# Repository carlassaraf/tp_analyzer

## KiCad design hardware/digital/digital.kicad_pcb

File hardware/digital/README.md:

# Placa digital: ADC de picos y expansor de E/S

Esta placa es el punto de unión entre las 4 placas analógicas (una por línea: L1, L2, L3 y N) y la placa del RP2350B. Todas las señales de las placas analógicas pasan por acá, así que hacia el RP2350B sale **un solo conector**.

- Esquemático: [digital.kicad_sch](digital.kicad_sch) (una hoja, A3).
- Placa analógica (una por línea): [../analog](../analog).

## 1. Qué hace

| Función | Cómo |
|---|---|
| Leer los detectores de pico (VPK, IPK) de las 4 líneas | Dos MCP3204 (12 bits, 4 canales, SPI): U2 para L1 y L2, U3 para L3 y N |
| Generar los 10 chip selects (8 MCP41010 + 2 MCP3204) sin usar pines del RP2350B | Expansor MCP23017 por I2C (U1) |
| Llevar las 8 señales del canal principal (VADC, IADC) al ADC del RP2350B | Pasan directo de J1–J4 a J5 |
| Repartir alimentación y SPI a las placas analógicas | J5 → J1–J4 |

```
 Placa analógica L1 ──┐ 2x07                                       2x13
 Placa analógica L2 ──┤   VADC, IADC ─────────────────────────────►┐
 Placa analógica L3 ──┤   VPK, IPK L1/L2 ──► U2 ──┐               │
 Placa analógica N  ──┘   VPK, IPK L3/N  ──► U3 ──┤ MISO          ├── J5 ──► RP2350B
              ▲  SCK/MOSI (33 Ω por línea) ◄────┤ SCK, MOSI        │         (ADC GPIO40-47,
              └─ CS_V, CS_I ◄── U1 MCP23017 ◄───┘ SDA, SCL ────────┘          SPI, I2C, 5 V, 3,3 V)
```

## 2. Conectores

### J1–J4: placas analógicas (2x07, IDC, cable plano)

Mismo pinout en la placa analógica. Cada señal analógica viaja entre dos GND del cable plano.

| Pin | Señal | Pin | Señal |
|---|---|---|---|
| 1 | VADC (canal principal de tensión) | 2 | GND |
| 3 | IADC (canal principal de corriente) | 4 | GND |
| 5 | VPK (detector de pico de tensión) | 6 | GND |
| 7 | IPK (detector de pico de corriente) | 8 | GND |
| 9 | SCK | 10 | MOSI |
| 11 | CS_V (MCP41010 de tensión) | 12 | CS_I (MCP41010 de corriente) |
| 13 | +3,3 V | 14 | +5 V |

J1 = L1, J2 = L2, J3 = L3, J4 = N. En el esquemático las redes llevan el sufijo de la línea: `VADC_L1`, `CS_I_N`, etc.

### J5: RP2350B (2x13, IDC)

| Pin | Señal | Pin | Señal |
|---|---|---|---|
| 1 | IADC_L1 | 2 | GND |
| 3 | VADC_L1 | 4 | GND |
| 5 | IADC_L2 | 6 | GND |
| 7 | VADC_L2 | 8 | GND |
| 9 | IADC_L3 | 10 | GND |
| 11 | VADC_L3 | 12 | GND |
| 13 | IADC_N | 14 | GND |
| 15 | VADC_N | 16 | GND |
| 17 | +5 V | 18 | SCK |
| 19 | +5 V | 20 | MISO |
| 21 | +3,3 V | 22 | MOSI |
| 23 | +3,3 V | 24 | SDA |
| 25 | GND | 26 | SCL |

Los pines 1–15 van a las entradas de ADC del RP2350B (GPIO40–47). Dentro de cada par, IADC va en el pin impar más bajo y VADC en el siguiente: es el orden en que llegan las pistas por el borde de la placa (ver [placa_pcb.md](placa_pcb.md)). El cable o adaptador hacia el devboard tiene que respetar esta tabla. La alimentación de todo el sistema analógico entra por J5.

Pines 17–26: la fila impar mira al borde de la placa y lleva solo alimentación y GND, que pasan por vía al lado del conector. La fila par mira al interior y lleva las cinco señales digitales, en el orden en que llegan a U2 y U1 sin cruzarse. En el cable plano cada señal digital queda entre dos hilos de alimentación o GND.

### J6: expansión (1x08)

GPB2–GPB7 del MCP23017 (libres), +3,3 V y GND.

## 3. Chip selects (MCP23017, dirección 0x20)

A2, A1 y A0 van a GND: dirección I2C **0x20**. RESET con pull-up de 10 kΩ (R9). INTA e INTB sin conectar.

| Pin del MCP23017 | Señal | Dispositivo |
|---|---|---|
| GPA0 | CS_V_L1 | MCP41010, canal de tensión L1 |
| GPA1 | CS_I_L1 | MCP41010, canal de corriente L1 |
| GPA2 | CS_V_L2 | MCP41010, canal de tensión L2 |
| GPA3 | CS_I_L2 | MCP41010, canal de corriente L2 |
| GPA4 | CS_V_L3 | MCP41010, canal de tensión L3 |
| GPA5 | CS_I_L3 | MCP41010, canal de corriente L3 |
| GPA6 | CS_V_N | MCP41010, canal de tensión N |
| GPA7 | CS_I_N | MCP41010, canal de corriente N |
| GPB0 | CS_ADC_L12 | U2, MCP3204 de picos de L1 y L2 |
| GPB1 | CS_ADC_L3N | U3, MCP3204 de picos de L3 y N |
| GPB2–GPB7 | — | Libres, en J6 |

- **Pull-ups de 10 kΩ en los 10 CS (R12–R21).** Después del encendido o de un reset, los pines del MCP23017 son entradas (alta impedancia). Sin pull-up, un CS podría quedar flotando en bajo y un MCP41010 tomaría basura del bus SPI como un cambio de ganancia. Con los pull-ups todo queda deseleccionado hasta que el firmware configura el expansor.
- **GPA7 y GPB7 son solo salida** en la hoja de datos actual del MCP23017. Acá se usan como salidas, así que no hay problema.

## 4. ADC de picos (MCP3204)

Cada MCP3204 lee las dos líneas que tiene al lado en la placa (U2: L1 y L2, U3: L3 y N), en lugar de separar tensión y corriente. Así los picos de cada par de conectores llegan juntos al ADC y se ahorran cruces en el ruteo (ver [placa_pcb.md](placa_pcb.md)). Para el firmware solo cambia el mapa de canales.

| ADC | CH0 | CH1 | CH2 | CH3 |
|---|---|---|---|---|
| U2 (L1, L2) | VPK_L1 | IPK_L1 | VPK_L2 | IPK_L2 |
| U3 (L3, N) | VPK_L3 | IPK_L3 | VPK_N | IPK_N |

- **VREF = 3,3 V, ratiométrico.** Las placas analógicas toman su 3,3 V de esta placa, y su VBIAS es 3,3 V / 2. Si el 3,3 V se mueve, VBIAS y la referencia se mueven juntos, y VBIAS sigue cayendo en ~2048 cuentas. El offset de cada canal (tolerancia del divisor de VBIAS y fuga del detector) se calibra midiendo sin señal.
- Rango: el detector entrega VBIAS + 0 a 1,3 V, o sea 1,65 a 2,95 V, dentro de 0–3,3 V. 1 LSB = 0,81 mV.
- **100 nF en cada entrada (C4–C7, C11–C14).** El capacitor de muestreo del MCP3204 (~20 pF) se carga de golpe al empezar la conversión; los 100 nF le dan esa carga sin que la tensión se mueva (20 pF / 100 nF → < 1 LSB). Con los 10 kΩ en serie de la placa analógica forman un filtro de τ = 1 ms, despreciable frente a la descarga del detector (0,47 s).
- **Desacople:** C8 / C15 (100 nF) en Vdd; C9 + C10 / C16 + C17 (1 µF + 100 nF) junto al pin Vref.
- **SPI ≤ 1 MHz** a 3,3 V (límite del MCP3204 con VDD = 2,7 V). Los MCP41010 aceptan hasta 10 MHz: el firmware configura la frecuencia por dispositivo.
- **MISO compartido.** Dout del MCP3204 queda en alta impedancia mientras CS está alto, así que U2 y U3 comparten MISO. Los MCP41010 no tienen salida SO. El ERC marca "Output–Output" entre los dos Dout; en el proyecto ese caso está bajado a advertencia porque es intencional.

## 5. SPI hacia las placas: 33 Ω en serie (R1–R8)

SCK y MOSI de cada línea pasan por 33 Ω (R1/R2 = L1, R3/R4 = L2, R5/R6 = L3, R7/R8 = N). El cable plano a cada placa es una línea de transmisión corta sin terminar. Sin resistencia, los flancos de SCK rebotan y pueden contar como un pulso de reloj extra en el MCP41010. Los 33 Ω, junto con la impedancia de salida del RP2350B, se acercan a la impedancia del cable y amortiguan el rebote. Además, cada línea queda aislada de las otras: un cortocircuito en un cable no tira abajo el SPI de todas.

## 6. I2C

Pull-ups de 4,7 kΩ en SDA y SCL (R10, R11). **No colocarlos si la placa del RP2350B ya tiene pull-ups** en ese bus. Con 4,7 kΩ y unos 100 pF de bus, 400 kHz funciona bien.

## 7. Consumo estimado (4 placas analógicas)

| Riel | Consumidor | Corriente |
|---|---|---|
| 3,3 V | Divisor de VBIAS, 4 × 165 µA | 0,7 mA |
| 3,3 V | MCP41010, 8 × ~1 µA | < 0,1 mA |
| 3,3 V | MCP3204, 2 × ~0,4 mA (convirtiendo) | 0,8 mA |
| 3,3 V | MCP23017 activo + un CS en bajo (0,33 mA) + I2C (0,7 mA en bajo) | ~2 mA |
| **3,3 V** | **Total** | **~4 mA** |
| 5 V | 3 LM358 por línea (~0,7 mA c/u) | 4 × 2 mA |
| 5 V | Pull-downs de 1 kΩ en las salidas de los LM358 (~1,65 mA c/u) | 4 × ~8 mA |
| **5 V** | **Total** | **~45 mA** |

C1 y C2 (10 µF) son la reserva de 3,3 V y 5 V en la entrada.

## 8. Notas para el firmware (Zephyr)

- Zephyr tiene drivers para los dos integrados: `microchip,mcp23017` (familia `mcp23xxx`, como controlador GPIO) y `microchip,mcp3204` (familia `mcp320x`, subsistema ADC).
- Los `cs-gpios` del bus SPI pueden apuntar a pines del MCP23017 (`<&mcp23017 0 GPIO_ACTIVE_LOW>`, etc.). Así los MCP3204 y los MCP41010 se declaran como dispositivos SPI normales.
- Cada transacción SPI cuesta dos escrituras I2C extra (bajar y subir el CS): unos 100–200 µs a 400 kHz. Alcanza para cambiar ganancias y para leer los picos cada ~100 ms. No sirve para muestreo rápido, que igual lo hace el ADC del RP2350B.
- Hay que configurar el MCP23017 (pines como salida en alto) antes de la primera transacción SPI. Hasta ese momento los pull-ups mantienen todo deseleccionado.

## 9. Lista de componentes

J1–J6 usan footprints de [tp_digital.pretty](tp_digital.pretty): los estándar con pads de 2,0 mm y agujero de 1,0 mm, para agujerear a mano.

R1, R3, R5, R6, R7, R10 y R20, y los capacitores C4, C7, C12 y C13, tienen pistas que pasan entre sus pads. Por eso las resistencias son 1206: no reemplazarlas ni a ellas ni a los capacitores por un tamaño menor (ver [placa_pcb.md](placa_pcb.md), sección 4).

| Ref. | Valor | Tipo | Función |
|---|---|---|---|
| U1 | MCP23017-E/SO | SOIC-28W | Expansor de E/S I2C (chip selects) |
| U2, U3 | MCP3204-CI/SL | SOIC-14 | ADC de picos (U2: L1 y L2, U3: L3 y N) |
| J1–J4 | 2x07 | IDC vertical, 2,54 mm | Placas analógicas L1, L2, L3, N |
| J5 | 2x13 | IDC vertical, 2,54 mm | RP2350B |
| J6 | 1x08 | Tira 2,54 mm | GPB2–GPB7 libres |
| R1–R8 | 33 Ω | 1206, 1 % | Serie en SCK y MOSI de cada línea |
| R9 | 10 kΩ | 1206, 1 % | Pull-up de RESET del MCP23017 |
| R10, R11 | 4,7 kΩ | 1206, 1 % | Pull-ups I2C (opcionales) |
| R12–R21 | 10 kΩ | 1206, 1 % | Pull-ups de los 10 chip selects |
| C1, C2 | 10 µF | 0805, X7R | Reserva de 3,3 V y 5 V |
| C3 | 100 nF | 0805, X7R | Desacople de U1 |
| C4–C7, C11–C14 | 100 nF | 0805, X7R | Entradas de los MCP3204 |
| C8, C15 | 100 nF | 0805, X7R | Desacople de Vdd de U2 y U3 |
| C9, C16 | 1 µF | 0805, X7R | Vref de U2 y U3 |
| C10, C17 | 100 nF | 0805, X7R | Vref de U2 y U3 |

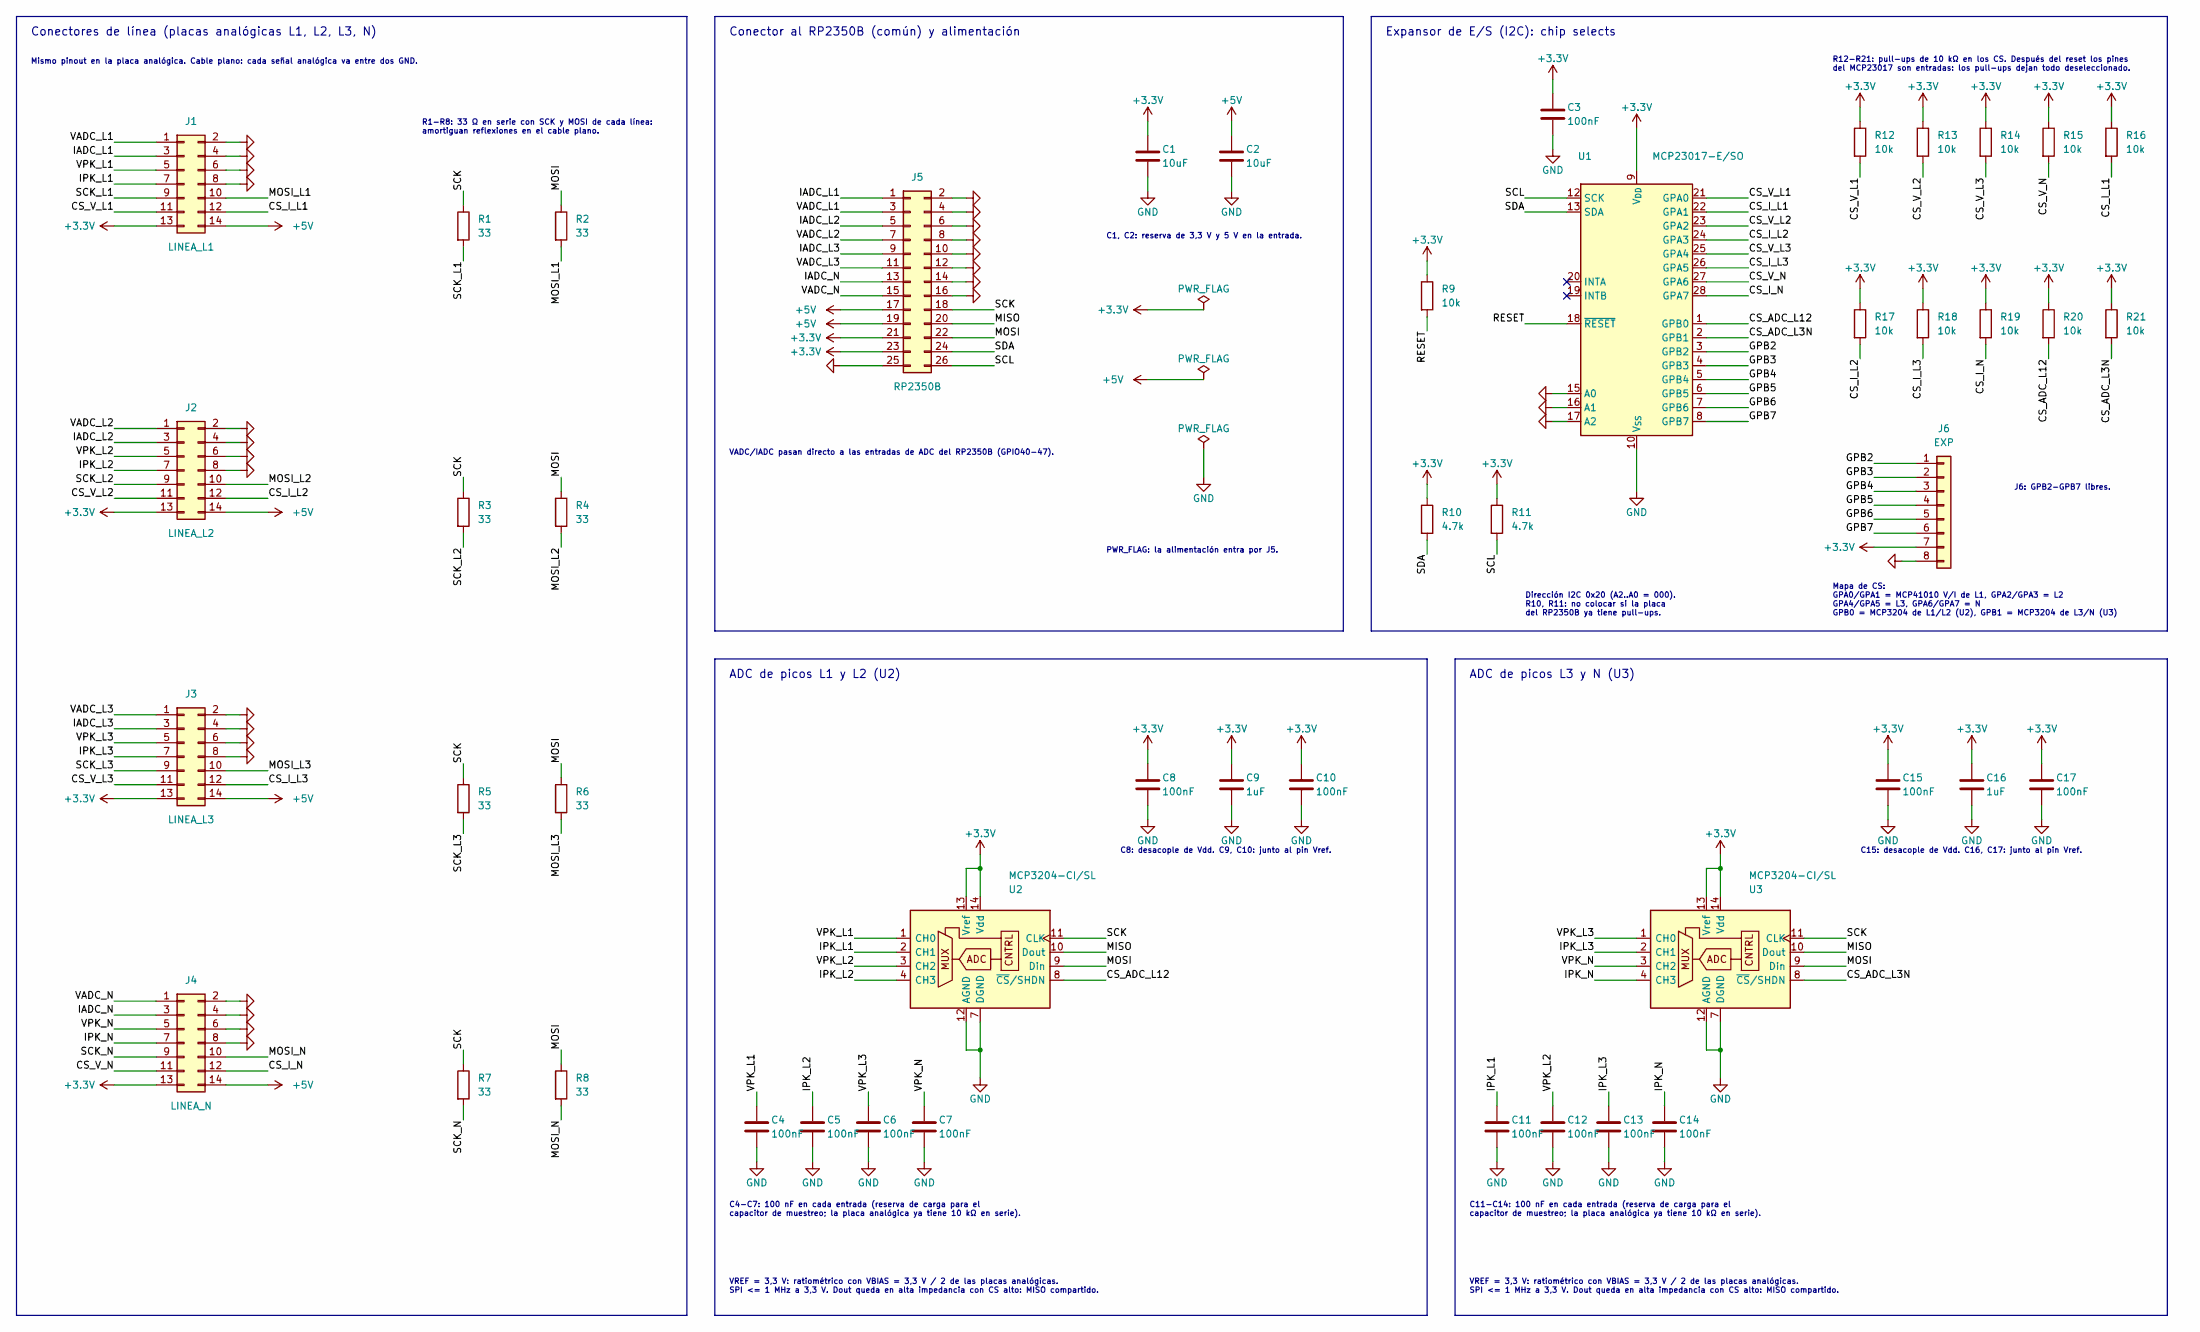
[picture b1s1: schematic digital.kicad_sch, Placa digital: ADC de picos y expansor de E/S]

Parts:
C1, C2: 10uF; C_0805_2012Metric
C3, C4, C5, C6, C7, C8, C10, C11, C12, C13, C14, C15, C17: 100nF; C_0805_2012Metric
C9, C16: 1uF; C_0805_2012Metric
J1: LINEA_L1; IDC-Header_2x07_P2.54mm_Vertical_HandEtched
J2: LINEA_L2; IDC-Header_2x07_P2.54mm_Vertical_HandEtched
J3: LINEA_L3; IDC-Header_2x07_P2.54mm_Vertical_HandEtched
J4: LINEA_N; IDC-Header_2x07_P2.54mm_Vertical_HandEtched
J5: RP2350B; IDC-Header_2x13_P2.54mm_Vertical_HandEtched
J6: EXP; PinHeader_1x08_P2.54mm_Vertical_HandEtched
R1, R2, R3, R4, R5, R6, R7, R8: 33; R_1206_3216Metric
R9, R12, R13, R14, R15, R16, R17, R18, R19, R20, R21: 10k; R_1206_3216Metric
R10, R11: 4.7k; R_1206_3216Metric
U1: MCP23017-E/SO; SOIC-28W_7.5x17.9mm_P1.27mm
U2, U3: MCP3204-CI/SL; SOIC-14_3.9x8.7mm_P1.27mm

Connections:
+3.3V: C1.1, C3.1, C8.1, C9.1, C10.1, C15.1, C16.1, C17.1, J1.13, J2.13, J3.13, J4.13, J5.21, J5.23, J6.7, R9.1, R10.1, R11.1, R12.1, R13.1, R14.1, R15.1, R16.1, R17.1, R18.1, R19.1, R20.1, R21.1, U1.9 (V_{DD}), U2.13 (Vref), U2.14 (Vdd), U3.13 (Vref), U3.14 (Vdd)
+5V: C2.1, J1.14, J2.14, J3.14, J4.14, J5.17, J5.19
/CS_ADC_L3N: R21.2, U1.2 (GPB1), U3.8 (~CS/SHDN)
/CS_ADC_L12: R20.2, U1.1 (GPB0), U2.8 (~CS/SHDN)
/CS_I_L1: J1.12, R16.2, U1.22 (GPA1)
/CS_I_L2: J2.12, R17.2, U1.24 (GPA3)
/CS_I_L3: J3.12, R18.2, U1.26 (GPA5)
/CS_I_N: J4.12, R19.2, U1.28 (GPA7)
/CS_V_L1: J1.11, R12.2, U1.21 (GPA0)
/CS_V_L2: J2.11, R13.2, U1.23 (GPA2)
/CS_V_L3: J3.11, R14.2, U1.25 (GPA4)
/CS_V_N: J4.11, R15.2, U1.27 (GPA6)
/GPB2: J6.1, U1.3 (GPB2)
/GPB3: J6.2, U1.4 (GPB3)
/GPB4: J6.3, U1.5 (GPB4)
/GPB5: J6.4, U1.6 (GPB5)
/GPB6: J6.5, U1.7 (GPB6)
/GPB7: J6.6, U1.8 (GPB7)
/IADC_L1: J1.3, J5.1
/IADC_L2: J2.3, J5.5
/IADC_L3: J3.3, J5.9
/IADC_N: J4.3, J5.13
/IPK_L1: C11.1, J1.7, U2.2 (CH1)
/IPK_L2: C5.1, J2.7, U2.4 (CH3)
/IPK_L3: C13.1, J3.7, U3.2 (CH1)
/IPK_N: C14.1, J4.7, U3.4 (CH3)
/MISO: J5.20, U2.10 (Dout), U3.10 (Dout)
/MOSI: J5.22, R2.1, R4.1, R6.1, R8.1, U2.9 (Din), U3.9 (Din)
/MOSI_L1: J1.10, R2.2
/MOSI_L2: J2.10, R4.2
/MOSI_L3: J3.10, R6.2
/MOSI_N: J4.10, R8.2
/RESET: R9.2, U1.18 (~RESET)
/SCK: J5.18, R1.1, R3.1, R5.1, R7.1, U2.11 (CLK), U3.11 (CLK)
/SCK_L1: J1.9, R1.2
/SCK_L2: J2.9, R3.2
/SCK_L3: J3.9, R5.2
/SCK_N: J4.9, R7.2
/SCL: J5.26, R11.2, U1.12 (SCK)
/SDA: J5.24, R10.2, U1.13 (SDA)
/VADC_L1: J1.1, J5.3
/VADC_L2: J2.1, J5.7
/VADC_L3: J3.1, J5.11
/VADC_N: J4.1, J5.15
/VPK_L1: C4.1, J1.5, U2.1 (CH0)
/VPK_L2: C12.1, J2.5, U2.3 (CH2)
/VPK_L3: C6.1, J3.5, U3.1 (CH0)
/VPK_N: C7.1, J4.5, U3.3 (CH2)
GND: C1.2, C2.2, C3.2, C4.2, C5.2, C6.2, C7.2, C8.2, C9.2, C10.2, C11.2, C12.2, C13.2, C14.2, C15.2, C16.2, C17.2, J1.2, J1.4, J1.6, J1.8, J2.2, J2.4, J2.6, J2.8, J3.2, J3.4, J3.6, J3.8, J4.2, J4.4, J4.6, J4.8, J5.2, J5.4, J5.6, J5.8, J5.10, J5.12, J5.14, J5.16, J5.25, J6.8, U1.10 (V_{SS}), U1.15 (A0), U1.16 (A1), U1.17 (A2), U2.7 (DGND), U2.12 (AGND), U3.7 (DGND), U3.12 (AGND)

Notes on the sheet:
ADC de picos L1 y L2 (U2)
J6: GPB2-GPB7 libres.
C15: desacople de Vdd. C16, C17: junto al pin Vref.
R12-R21: pull-ups de 10 kΩ en los CS. Después del reset los pines del MCP23017 son entradas: los pull-ups dejan todo deseleccionado.
ADC de picos L3 y N (U3)
C8: desacople de Vdd. C9, C10: junto al pin Vref.
VADC/IADC pasan directo a las entradas de ADC del RP2350B (GPIO40-47).
C1, C2: reserva de 3,3 V y 5 V en la entrada.
Mapa de CS: GPA0/GPA1 = MCP41010 V/I de L1, GPA2/GPA3 = L2 GPA4/GPA5 = L3, GPA6/GPA7 = N GPB0 = MCP3204 de L1/L2 (U2), GPB1 = MCP3204 de L3/N (U3)
VREF = 3,3 V: ratiométrico con VBIAS = 3,3 V / 2 de las placas analógicas. SPI <= 1 MHz a 3,3 V. Dout queda en alta impedancia con CS alto: MISO compartido.
Dirección I2C 0x20 (A2..A0 = 000). R10, R11: no colocar si la placa del RP2350B ya tiene pull-ups.
C11-C14: 100 nF en cada entrada (reserva de carga para el capacitor de muestreo; la placa analógica ya tiene 10 kΩ en serie).
Conector al RP2350B (común) y alimentación
Conectores de línea (placas analógicas L1, L2, L3, N)
C4-C7: 100 nF en cada entrada (reserva de carga para el capacitor de muestreo; la placa analógica ya tiene 10 kΩ en serie).
PWR_FLAG: la alimentación entra por J5.
Expansor de E/S (I2C): chip selects
Mismo pinout en la placa analógica. Cable plano: cada señal analógica va entre dos GND.
R1-R8: 33 Ω en serie con SCK y MOSI de cada línea: amortiguan reflexiones en el cable plano.

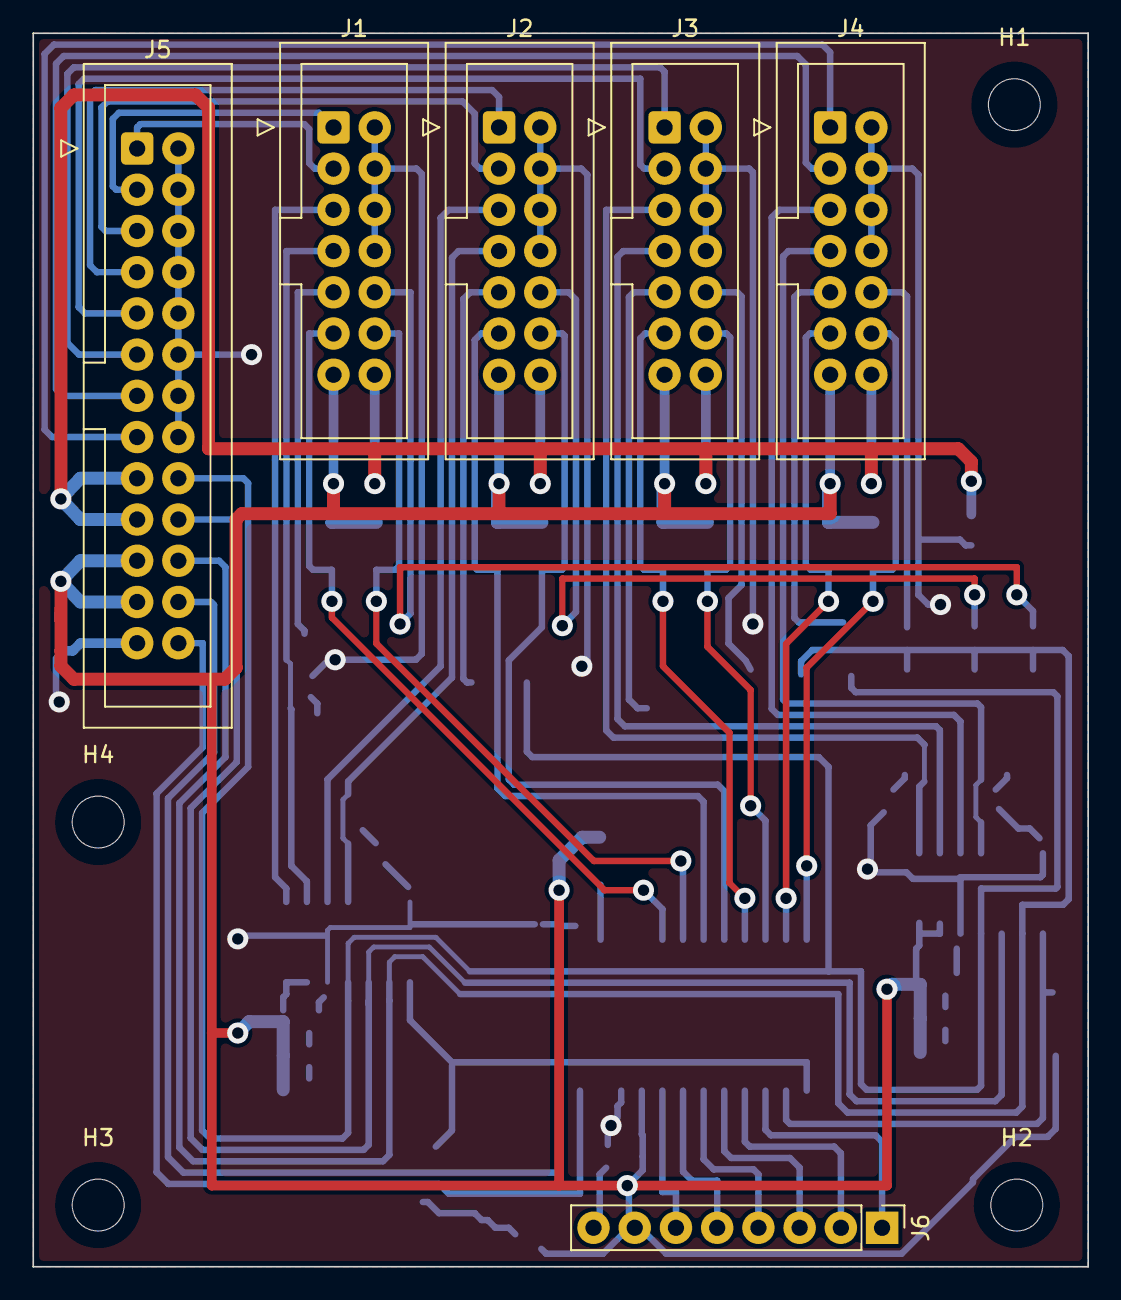
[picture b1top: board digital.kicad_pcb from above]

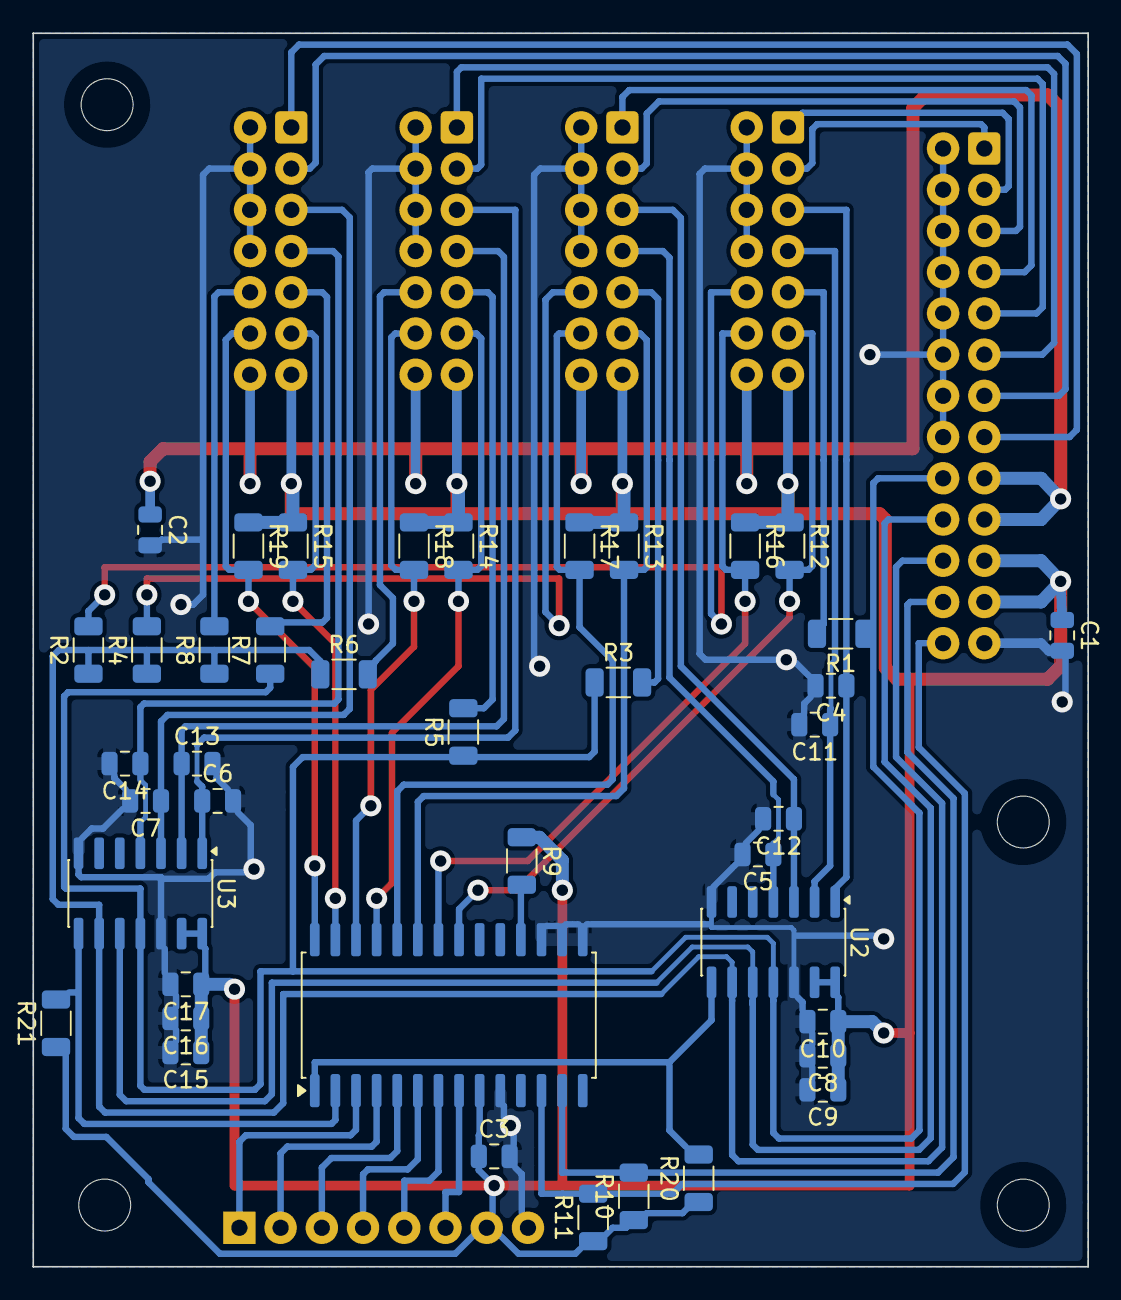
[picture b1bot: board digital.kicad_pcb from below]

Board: 2 copper layers, 65.0 x 76.0 mm, 51 parts (41 on the bottom side), 49 nets.

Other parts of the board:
H1, H2, H3, H4: MountingHole_3.2mm_M3

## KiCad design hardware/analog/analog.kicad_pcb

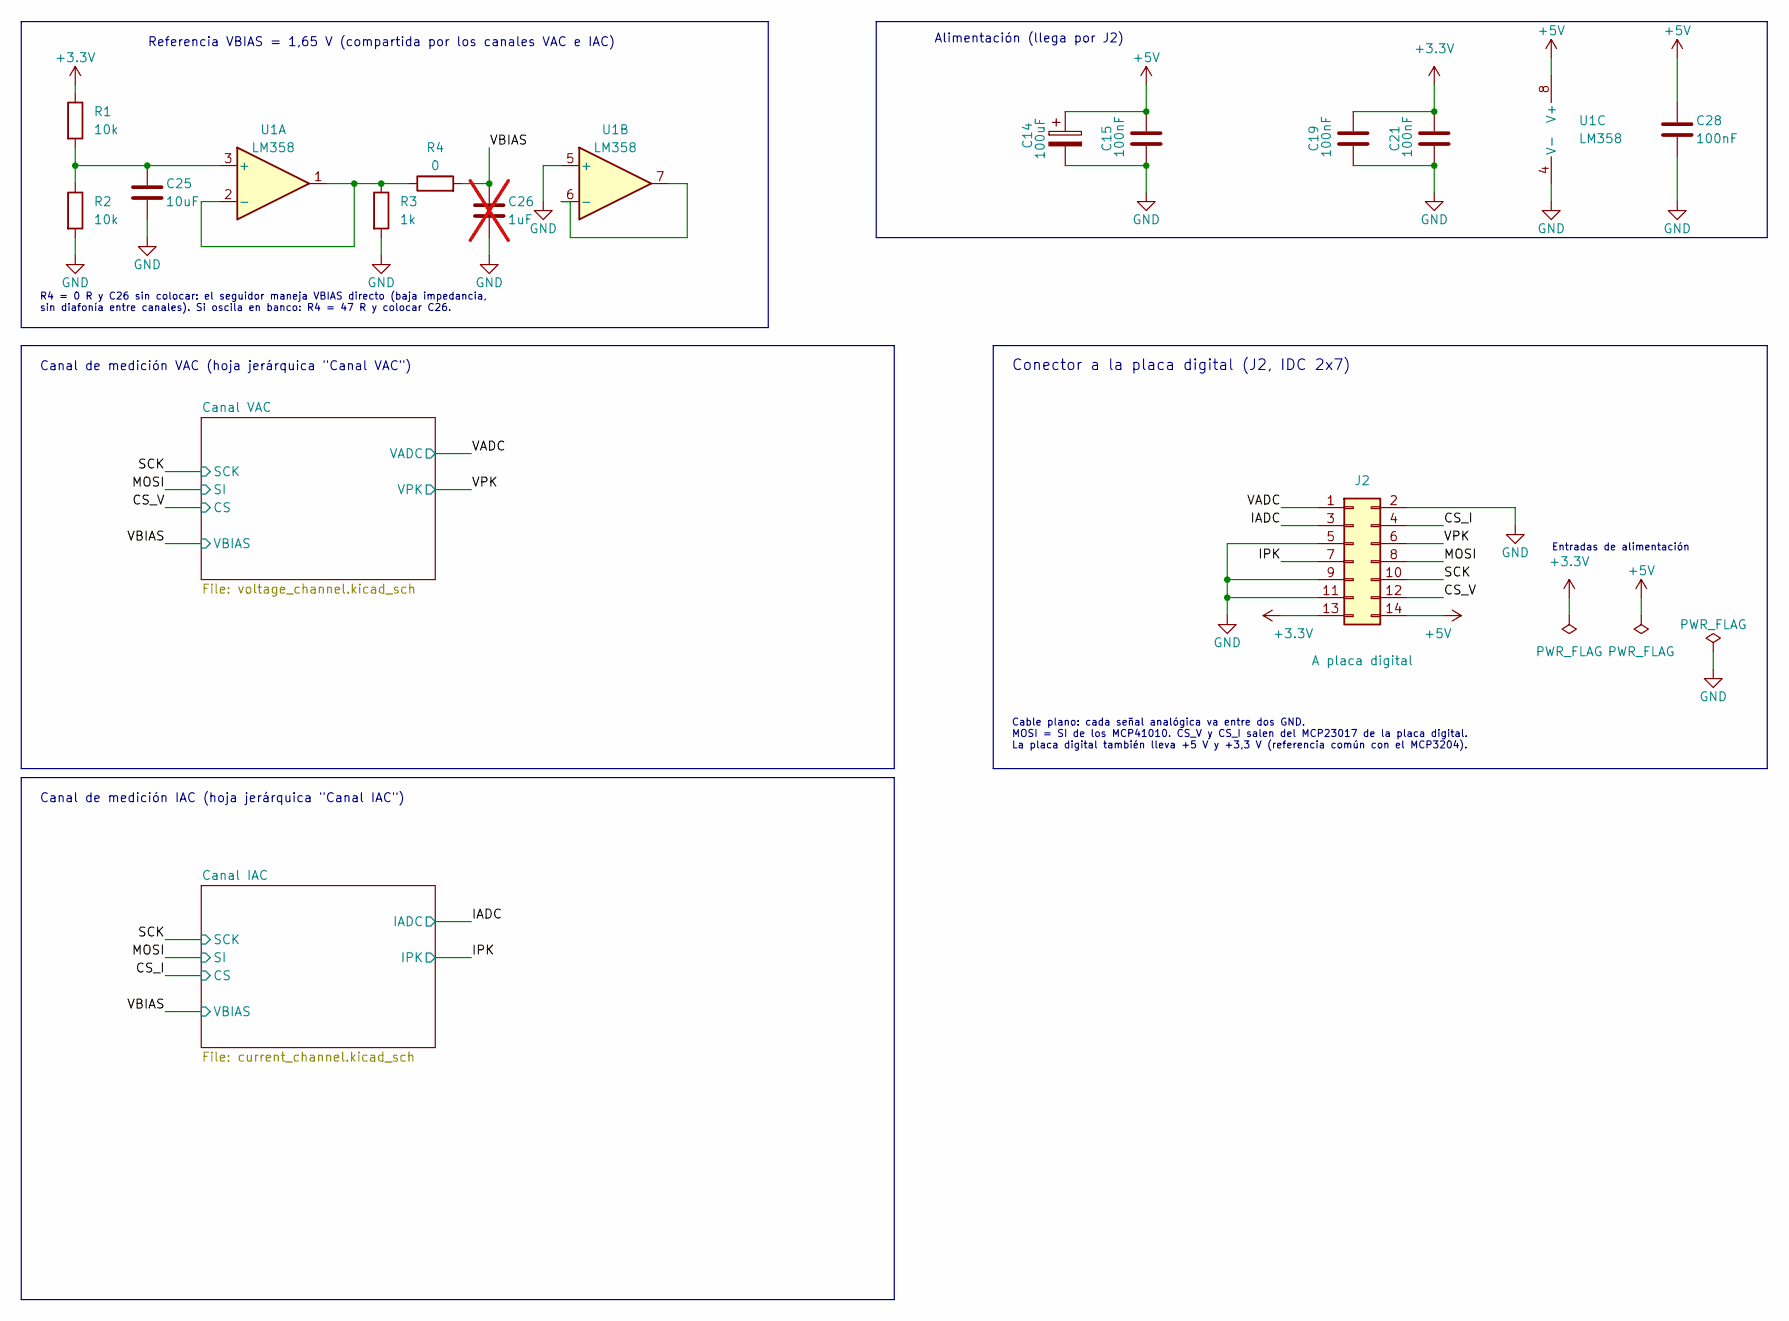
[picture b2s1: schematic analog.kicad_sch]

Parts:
C14: 100uF; CP_Elec_6.3x5.4
C15, C19, C21, C28: 100nF; C_0805_2012Metric
C25: 10uF; C_0805_2012Metric
C26: 1uF; C_0805_2012Metric; not fitted
J2: A placa digital; IDC-Header_2x07_P2.54mm_Vertical
R1, R2: 10k; R_0805_2012Metric
R3: 1k; R_0805_2012Metric
R4: 0; R_0805_2012Metric
U1: LM358; SOIC-8_3.9x4.9mm_P1.27mm

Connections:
+3.3V: C19.1, C21.1, J2.13, R1.1; also elsewhere on the board
+5V: C14.1, C15.1, C28.1, J2.14, U1.8 (V+); also elsewhere on the board
/CS_I: J2.12; also elsewhere on the board
/IADC: J2.3; also elsewhere on the board
/IPK: J2.7; also elsewhere on the board
/MOSI: J2.10; also elsewhere on the board
/VADC: J2.1; also elsewhere on the board
/VBIAS: C26.1, R4.2; also elsewhere on the board
unnamed: C25.1, R1.2, R2.1, U1.3 (+)
unnamed: R3.1, R4.1, U1.1, U1.2 (-)
unnamed: U1.6 (-), U1.7

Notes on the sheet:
Alimentación (llega por J2)
Canal de medición IAC (hoja jerárquica "Canal IAC")
Entradas de alimentación
R4 = 0 R y C26 sin colocar: el seguidor maneja VBIAS directo (baja impedancia, sin diafonía entre canales). Si oscila en banco: R4 = 47 R y colocar C26.
Canal de medición VAC (hoja jerárquica "Canal VAC")
Referencia VBIAS = 1,65 V (compartida por los canales VAC e IAC)
Conector a la placa digital (J2, IDC 2x7)
Cable plano: cada señal analógica va entre dos GND. MOSI = SI de los MCP41010. CS_V y CS_I salen del MCP23017 de la placa digital. La placa digital también lleva +5 V y +3,3 V (referencia común con el MCP3204).

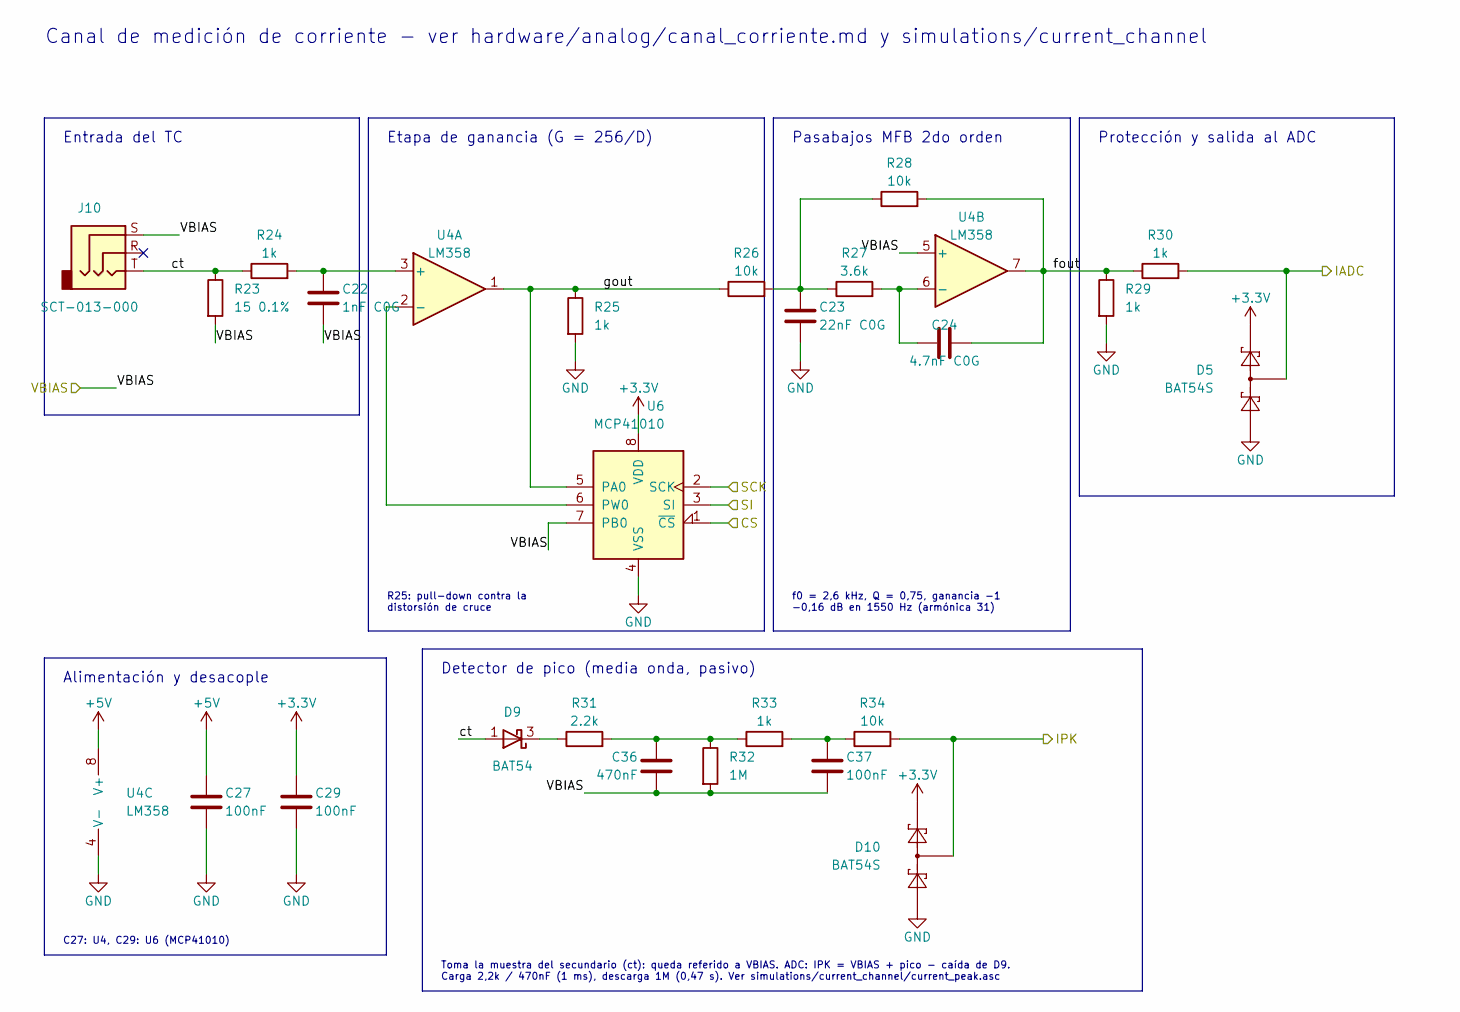
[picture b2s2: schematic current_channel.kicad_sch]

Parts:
C22: 1nF C0G; C_0805_2012Metric
C23: 22nF C0G; C_0805_2012Metric
C24: 4.7nF C0G; C_0805_2012Metric
C27, C29, C37: 100nF; C_0805_2012Metric
C36: 470nF; C_0805_2012Metric
D5, D10: BAT54S; SOT-23
D9: BAT54; SOT-23
J10: SCT-013-000; Jack_3.5mm_CUI_SJ1-3523N_Horizontal
R23: 15 0.1%; R_1206_3216Metric
R24, R25, R29, R30, R33: 1k; R_0805_2012Metric
R26, R28, R34: 10k; R_0805_2012Metric
R27: 3.6k; R_0805_2012Metric
R31: 2.2k; R_0805_2012Metric
R32: 1M; R_0805_2012Metric
U4: LM358; SOIC-8_3.9x4.9mm_P1.27mm
U6: MCP41010; SOIC-8_3.9x4.9mm_P1.27mm

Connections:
+3.3V: C29.1, D5.2 (K), D10.2 (K), U6.8 (VDD); also elsewhere on the board
+5V: C27.1, U4.8 (V+); also elsewhere on the board
/CS_I: U6.1 (~CS); also elsewhere on the board
/Canal IAC/ct: D9.1 (A), J10.T, R23.1, R24.1
/Canal IAC/fout: C24.2, R28.2, R29.1, R30.1, U4.7
/Canal IAC/gout: R25.1, R26.1, U4.1, U6.5 (PA0)
/IADC: D5.3 (COM), R30.2; also elsewhere on the board
/IPK: D10.3 (COM), R34.2; also elsewhere on the board
/MOSI: U6.3 (SI); also elsewhere on the board
/VBIAS: C22.2, C36.2, C37.2, J10.S, R23.2, R32.2, U4.5 (+), U6.7 (PB0); also elsewhere on the board
unnamed: C23.1, R26.2, R27.1, R28.1
unnamed: C36.1, R31.2, R32.1, R33.1
unnamed: C37.1, R33.2, R34.1
unnamed: D9.3 (K), R31.1
unnamed: C22.1, R24.2, U4.3 (+)
unnamed: U4.2 (-), U6.6 (PW0)
unnamed: C24.1, R27.2, U4.6 (-)

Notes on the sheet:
Alimentación y desacople
Detector de pico (media onda, pasivo)
R25: pull-down contra la distorsión de cruce
Pasabajos MFB 2do orden
Protección y salida al ADC
Canal de medición de corriente - ver hardware/analog/canal_corriente.md y simulations/current_channel
f0 = 2,6 kHz, Q = 0,75, ganancia -1 -0,16 dB en 1550 Hz (armónica 31)
Toma la muestra del secundario (ct): queda referido a VBIAS. ADC: IPK = VBIAS + pico - caída de D9. Carga 2,2k / 470nF (1 ms), descarga 1M (0,47 s). Ver simulations/current_channel/current_peak.asc
Etapa de ganancia (G = 256/D)
Entrada del TC
C27: U4, C29: U6 (MCP41010)

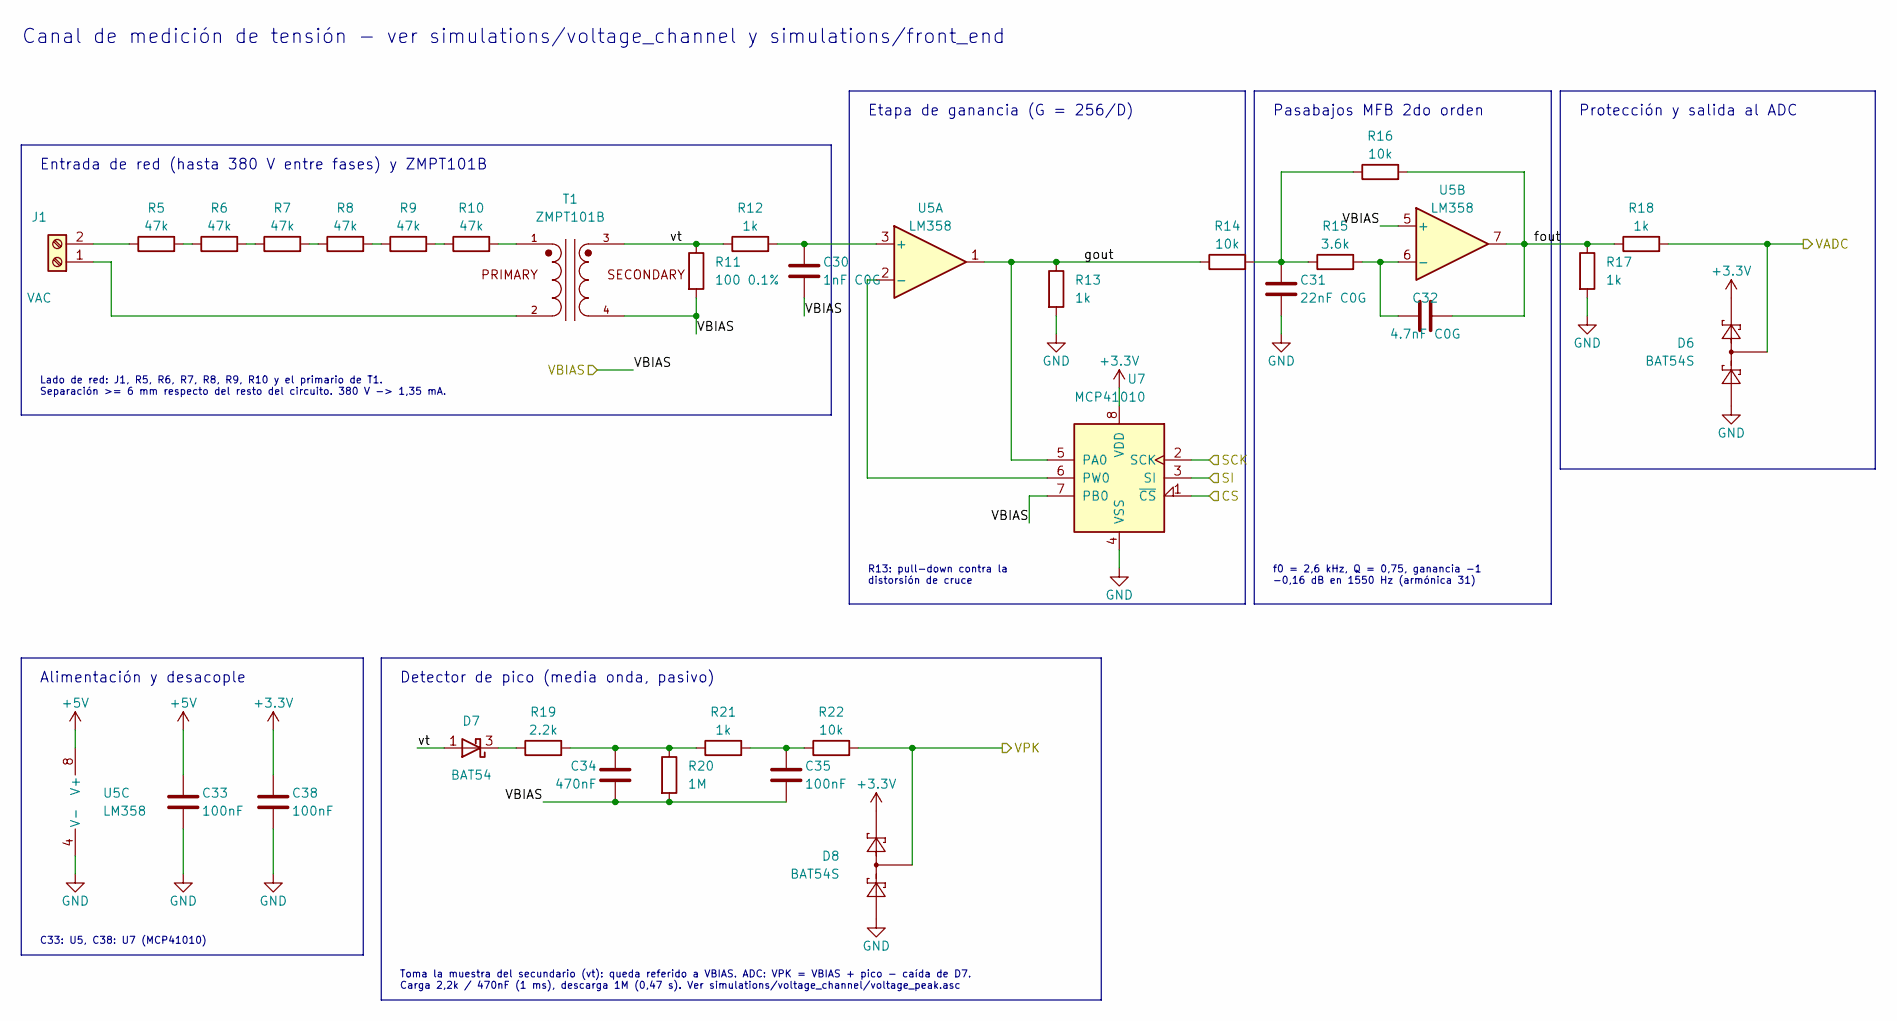
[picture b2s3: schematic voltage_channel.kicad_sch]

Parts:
C30: 1nF C0G; C_0805_2012Metric
C31: 22nF C0G; C_0805_2012Metric
C32: 4.7nF C0G; C_0805_2012Metric
C33, C35, C38: 100nF; C_0805_2012Metric
C34: 470nF; C_0805_2012Metric
D6, D8: BAT54S; SOT-23
D7: BAT54; SOT-23
J1: VAC; SolderWire_HV_1x02_P7.50mm_D1.3mm_OD3.0mm
R5, R6, R7, R8, R9, R10: 47k; R_1206_3216Metric
R11: 100 0.1%; R_0805_2012Metric
R12, R13, R17, R18, R21: 1k; R_0805_2012Metric
R14, R16, R22: 10k; R_0805_2012Metric
R15: 3.6k; R_0805_2012Metric
R19: 2.2k; R_0805_2012Metric
R20: 1M; R_0805_2012Metric
T1: ZMPT101B; Transformer_Zeming_ZMPT101K_HandEtched
U5: LM358; SOIC-8_3.9x4.9mm_P1.27mm
U7: MCP41010; SOIC-8_3.9x4.9mm_P1.27mm

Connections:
+3.3V: C38.1, D6.2 (K), D8.2 (K), U7.8 (VDD); also elsewhere on the board
+5V: C33.1, U5.8 (V+); also elsewhere on the board
/Canal VAC/fout: C32.2, R16.2, R17.1, R18.1, U5.7
/Canal VAC/gout: R13.1, R14.1, U5.1, U7.5 (PA0)
/Canal VAC/vt: D7.1 (A), R11.1, R12.1, T1.3
/MOSI: U7.3 (SI); also elsewhere on the board
/VADC: D6.3 (COM), R18.2; also elsewhere on the board
/VBIAS: C30.2, C34.2, C35.2, R11.2, R20.2, T1.4, U5.5 (+), U7.7 (PB0); also elsewhere on the board
unnamed: C31.1, R14.2, R15.1, R16.1
unnamed: C34.1, R19.2, R20.1, R21.1
unnamed: C35.1, R21.2, R22.1
unnamed: D7.3 (K), R19.1
unnamed: J1.1, T1.2
unnamed: J1.2, R5.1
unnamed: R5.2, R6.1
unnamed: R6.2, R7.1
unnamed: R7.2, R8.1
unnamed: R8.2, R9.1
unnamed: R9.2, R10.1
unnamed: R10.2, T1.1
unnamed: C30.1, R12.2, U5.3 (+)
unnamed: U5.2 (-), U7.6 (PW0)
unnamed: C32.1, R15.2, U5.6 (-)

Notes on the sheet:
f0 = 2,6 kHz, Q = 0,75, ganancia -1 -0,16 dB en 1550 Hz (armónica 31)
C33: U5, C38: U7 (MCP41010)
Entrada de red (hasta 380 V entre fases) y ZMPT101B
Etapa de ganancia (G = 256/D)
Pasabajos MFB 2do orden
R13: pull-down contra la distorsión de cruce
Lado de red: J1, R5, R6, R7, R8, R9, R10 y el primario de T1. Separación >= 6 mm respecto del resto del circuito. 380 V -> 1,35 mA.
Canal de medición de tensión - ver simulations/voltage_channel y simulations/front_end
Protección y salida al ADC
Toma la muestra del secundario (vt): queda referido a VBIAS. ADC: VPK = VBIAS + pico - caída de D7. Carga 2,2k / 470nF (1 ms), descarga 1M (0,47 s). Ver simulations/voltage_channel/voltage_peak.asc
Alimentación y desacople
Detector de pico (media onda, pasivo)

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
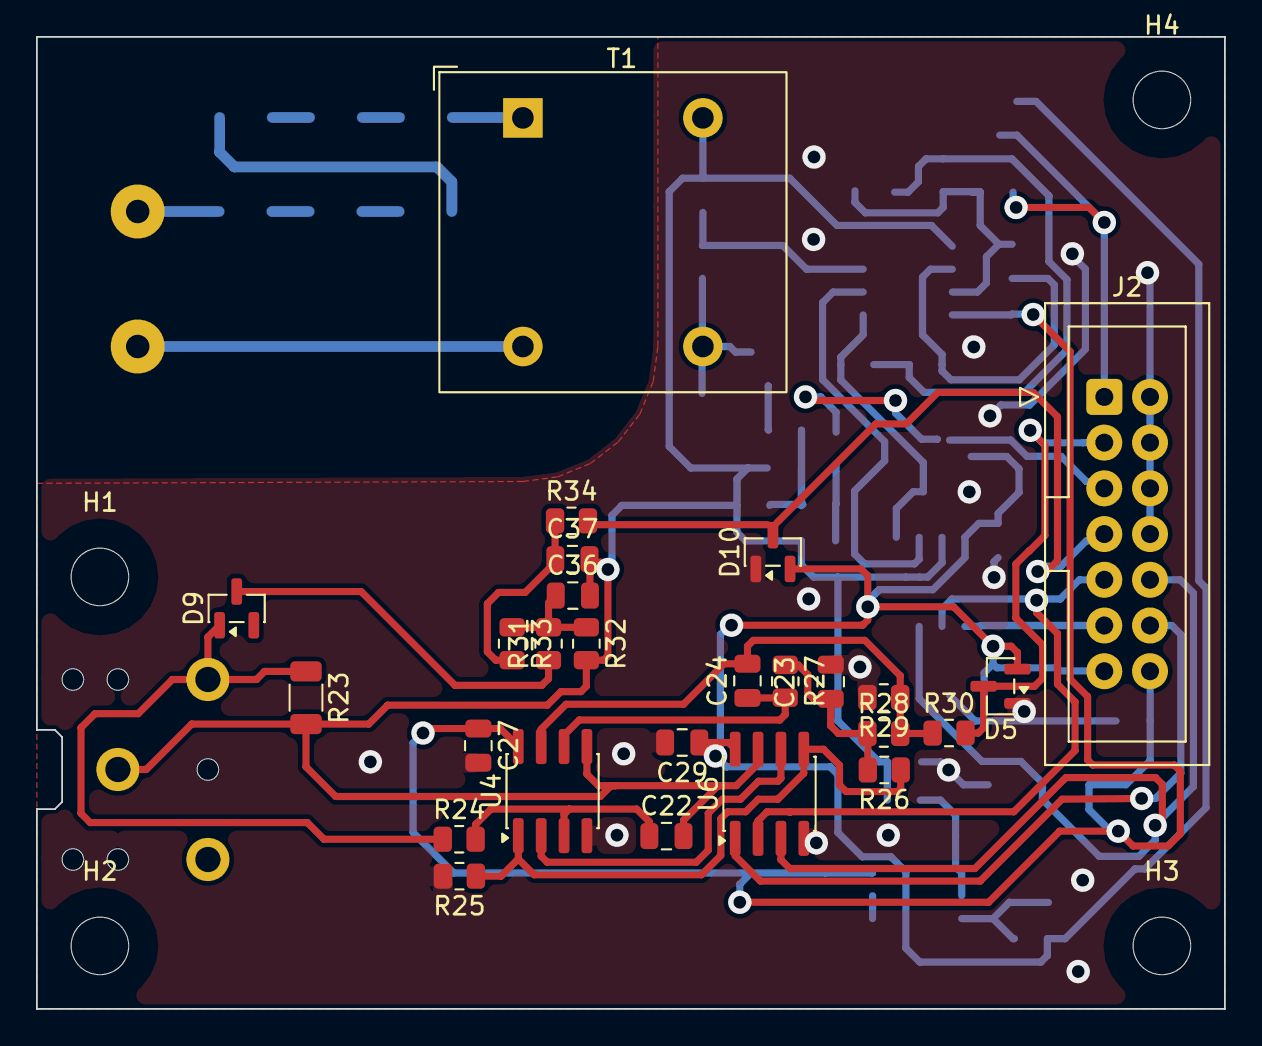
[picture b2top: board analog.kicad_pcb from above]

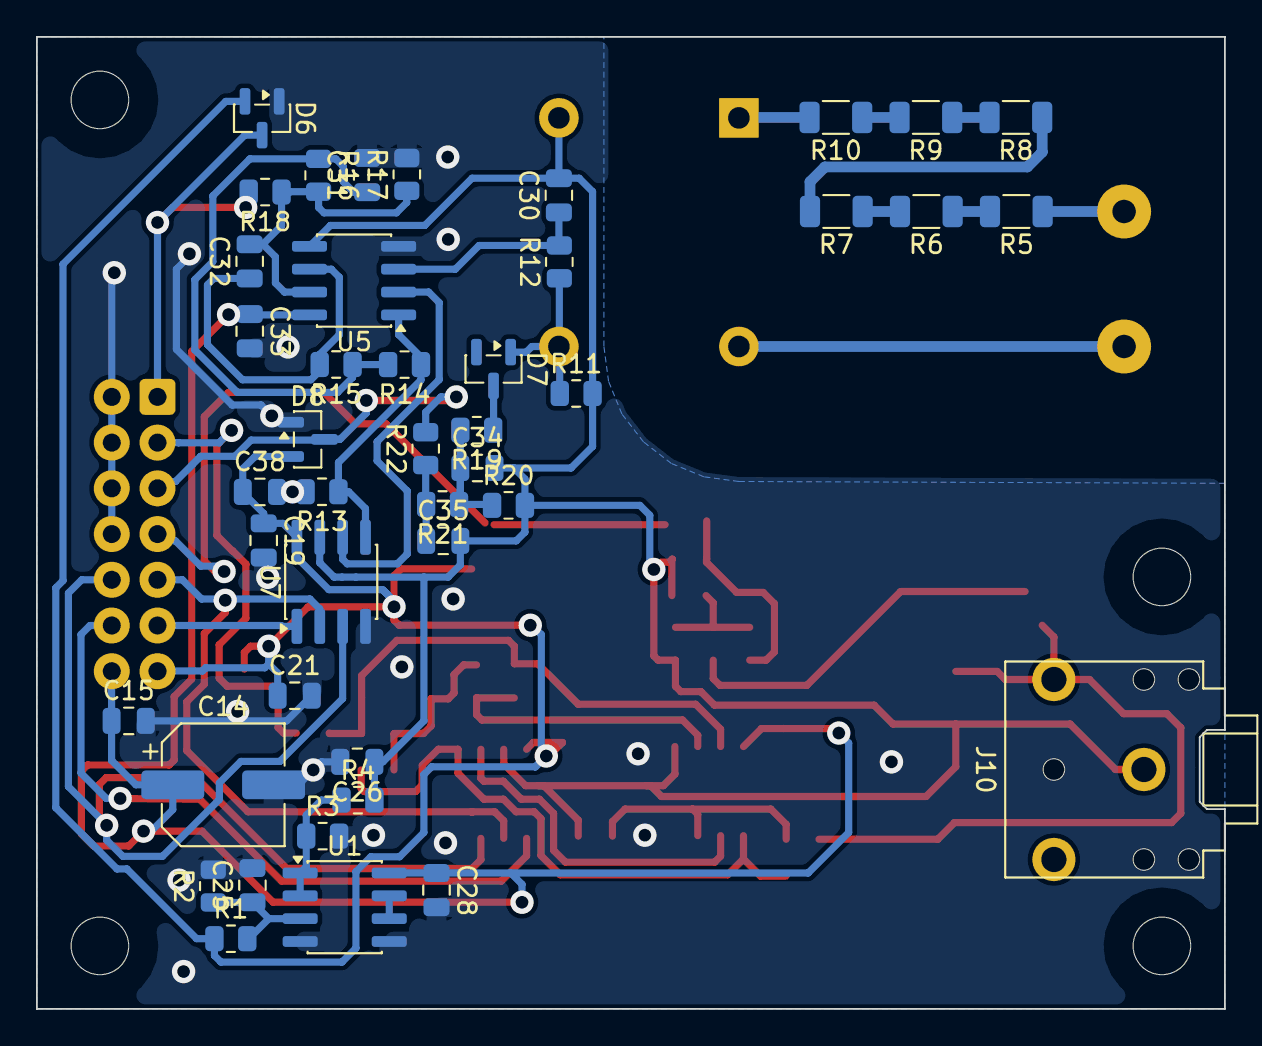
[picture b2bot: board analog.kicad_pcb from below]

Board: 2 copper layers, 66.0 x 54.0 mm, 74 parts (43 on the bottom side), 43 nets.

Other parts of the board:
H1, H2, H3, H4: M3; MountingHole_3.2mm_M3
